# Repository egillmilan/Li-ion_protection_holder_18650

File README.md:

# Li-ion protection holder
A protection circuit for a single 18650 lithium-ion cell. The circuit protects the battery from over-voltage (4.225V), under-voltage (3.2V), over-current discharge (~5A) and over-current charging (~5A). The protection thresholds depend on the choice of MOSFETs and the version of the AP9101C protection IC that is being used.

The device also acts as a battery holder for easy integration into various projects. The pin header holes are spaced 2.54mm apart which enables the holder to be soldered onto common perforated prototyping boards or it can even be plugged into breadboards.

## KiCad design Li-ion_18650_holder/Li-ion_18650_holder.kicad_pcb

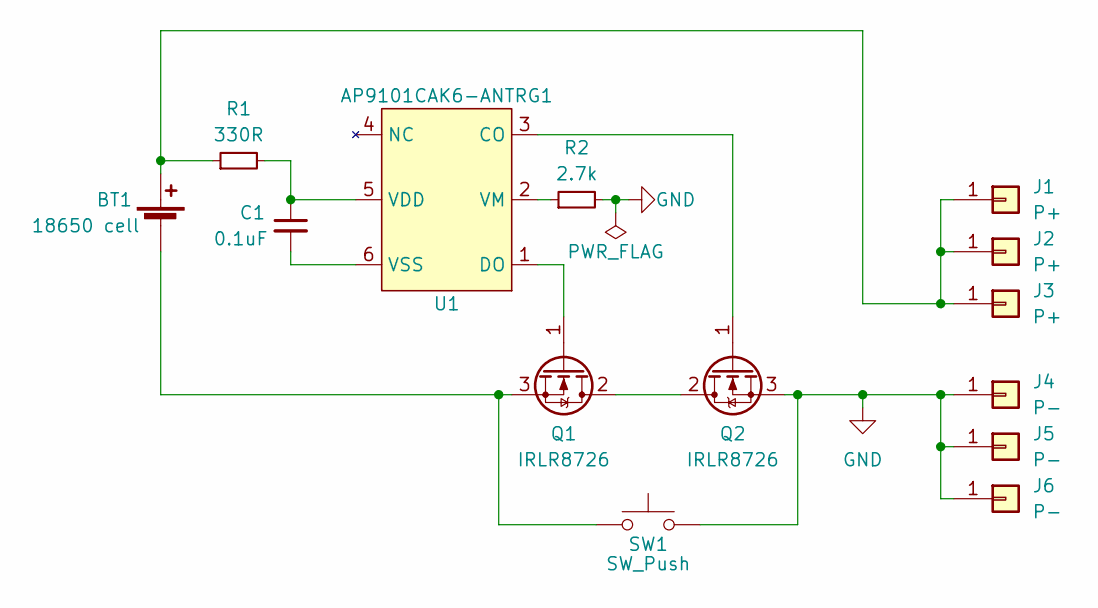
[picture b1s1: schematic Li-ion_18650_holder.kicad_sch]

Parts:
BT1: 18650 cell; Keystone_254_holder
C1: 0.1uF; C_1206_3216Metric_Pad1.33x1.80mm_HandSolder
J1, J3: P+; PinSocket_1x06_P2.54mm_Vertical
J2: P+; PinSocket_1x07_P2.54mm_Vertical
J4, J6: P-; PinSocket_1x06_P2.54mm_Vertical
J5: P-; PinSocket_1x07_P2.54mm_Vertical
Q1, Q2: IRLR8726; TO-252-2
R1: 330R; R_1206_3216Metric_Pad1.30x1.75mm_HandSolder
R2: 2.7k; R_1206_3216Metric_Pad1.30x1.75mm_HandSolder
SW1: SW_Push; TL3342F260QG
U1: AP9101CAK6-ANTRG1; SOT-23-6_Handsoldering

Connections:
GND: J4.1, J5.1, J6.1, Q2.3 (S), R2.2, SW1.2
unnamed: BT1.1 (+), J1.1, J2.1, J3.1, R1.1
unnamed: BT1.2 (-), Q1.3 (S), SW1.1
unnamed: C1.1, R1.2, U1.5 (VDD)
unnamed: C1.2, U1.6 (VSS)
unnamed: Q1.1 (G), U1.1 (DO)
unnamed: Q1.2 (D), Q2.2 (D)
unnamed: Q2.1 (G), U1.3 (CO)
unnamed: R2.1, U1.2 (VM)

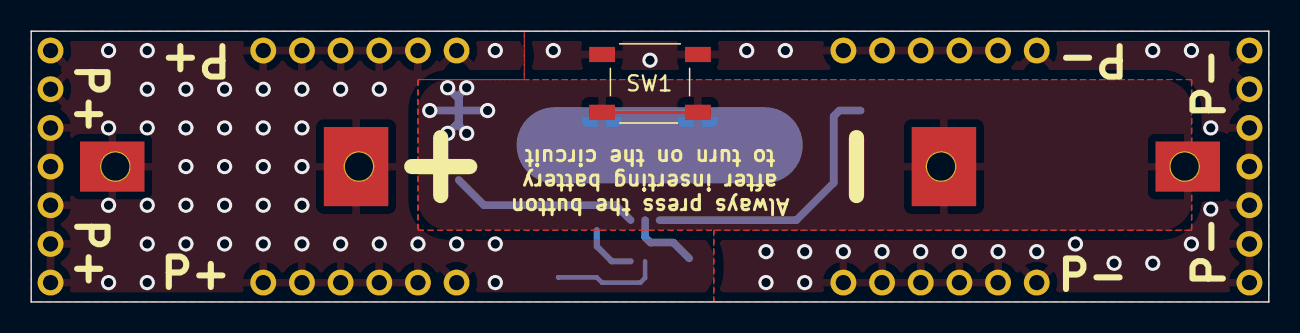
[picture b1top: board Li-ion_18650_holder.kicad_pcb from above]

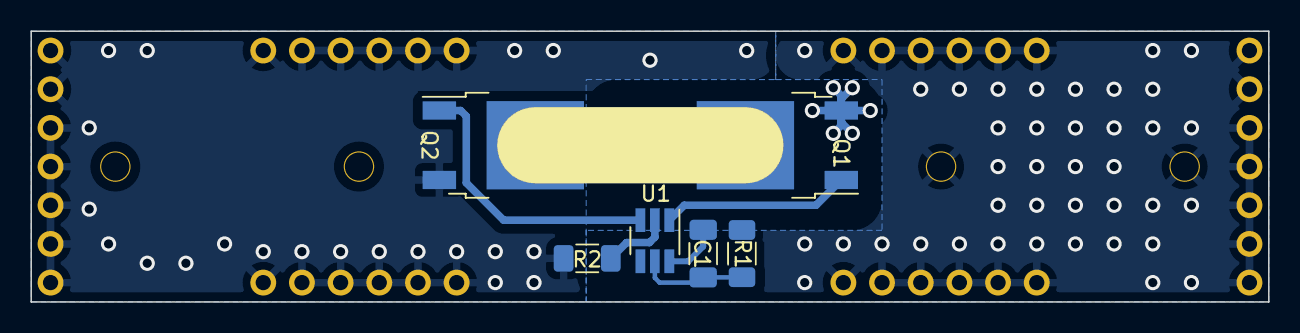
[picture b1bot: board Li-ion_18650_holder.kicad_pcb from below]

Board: 2 copper layers, 81.3 x 17.8 mm, 14 parts (12 on the bottom side), 9 nets.

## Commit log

2021-12-12 Added stitching between pours and pulled copper back from edges
